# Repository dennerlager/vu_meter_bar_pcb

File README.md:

# vu_meter_bar_pcb
pi hat for vu meter bar

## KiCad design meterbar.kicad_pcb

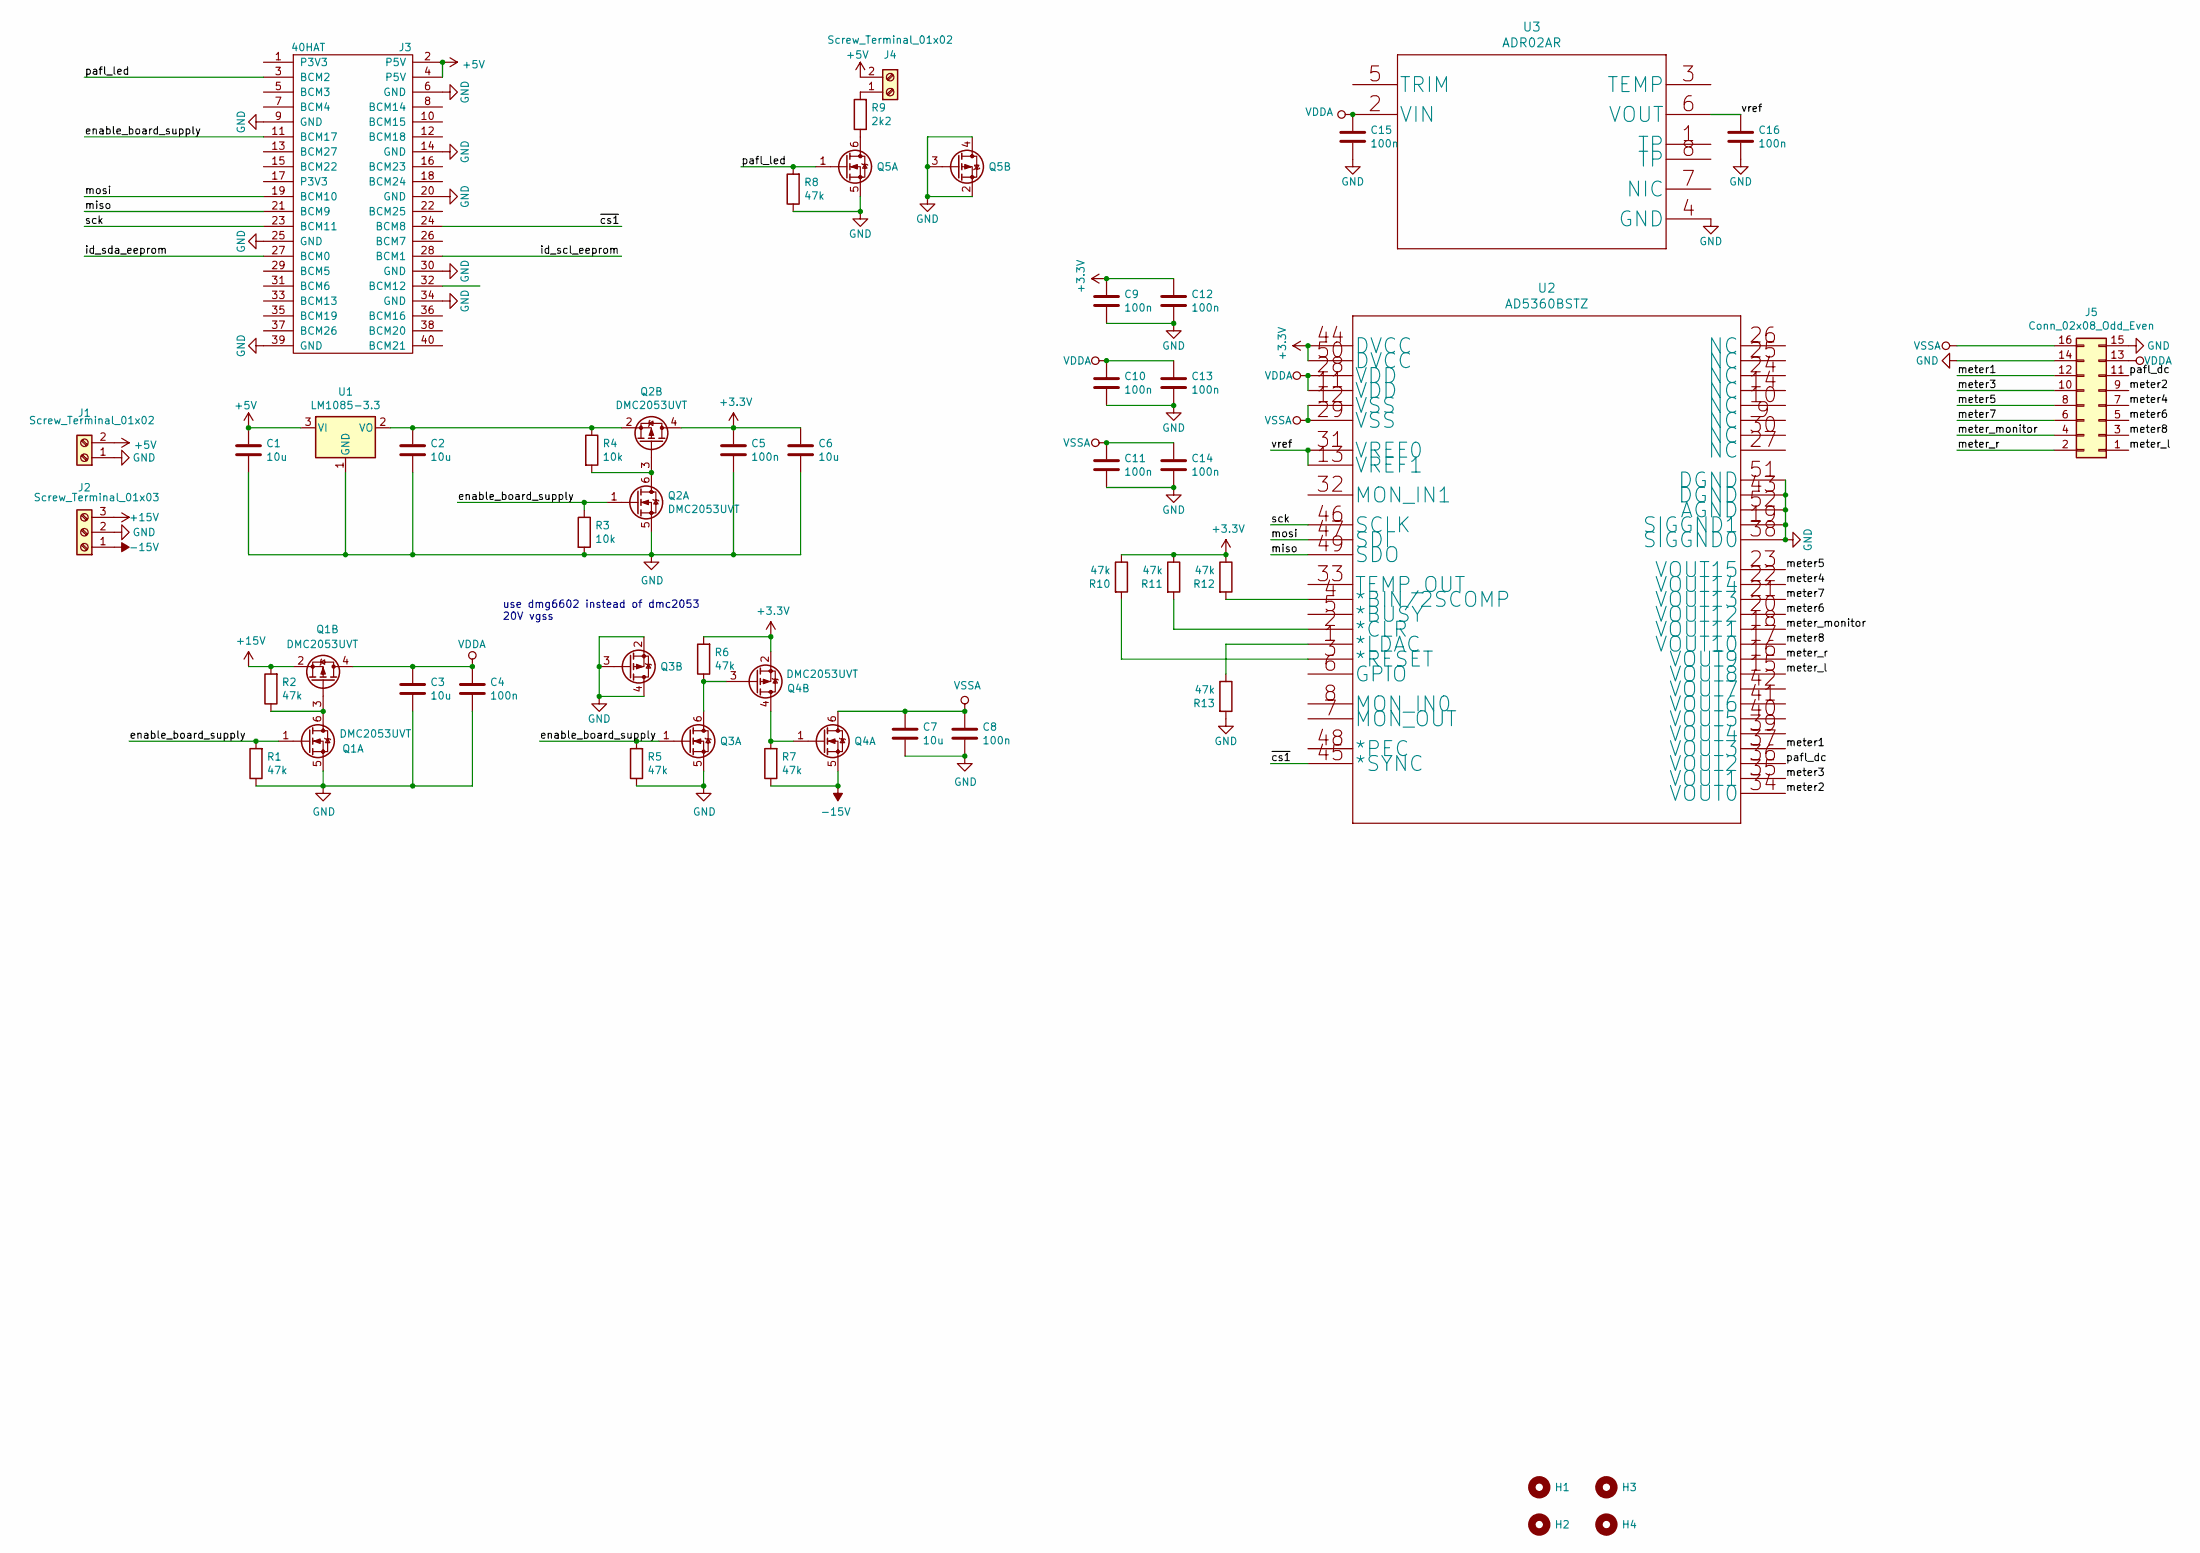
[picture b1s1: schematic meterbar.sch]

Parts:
C1, C2, C3, C6, C7: 10u; C_1206_3216Metric_Pad1.42x1.75mm_HandSolder; Voltage 20V
C4, C5, C8, C9, C10, C11, C12, C13, C14, C15, C16: 100n; C_0805_2012Metric_Pad1.15x1.40mm_HandSolder
H1, H2, H3, H4: MountingHole; MountingHole_3.2mm_M3
J1, J4: Screw_Terminal_01x02; TerminalBlock_bornier-2_P5.08mm
J2: Screw_Terminal_01x03; TerminalBlock_bornier-3_P5.08mm
J3: 40HAT; PinSocket_2x20_P2.54mm_Vertical
J5: Conn_02x08_Odd_Even; PinSocket_2x08_P2.54mm_Vertical
Q1, Q2, Q3, Q4, Q5: DMC2053UVT; TSOT-23-6
R1, R2, R5, R6, R7, R8, R10, R11, R12, R13: 47k; R_0805_2012Metric_Pad1.15x1.40mm_HandSolder
R3, R4: 10k; R_0805_2012Metric_Pad1.15x1.40mm_HandSolder
R9: 2k2; R_0805_2012Metric_Pad1.15x1.40mm_HandSolder
U1: LM1085-3.3; TO-220-3_Horizontal_TabDown
U2: AD5360BSTZ
U3: ADR02AR; ADR02ARZ

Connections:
+3V3: C5.1, C6.1, C9.1, C12.1, Q2.4 (D), Q4.2 (S), R6.2, R10.1, R11.1, R12.1, U2.44 (DVCC), U2.50 (DVCC)
+5V: C1.1, J1.2, J3.2 (P5V), J3.4 (P5V), J4.2, U1.3 (VI)
+15V: J2.3, Q1.2 (S), R2.2
-15V: J2.1, Q4.5 (S), R7.1
/enable_board_supply: J3.11 (BCM17), Q1.1 (G), Q2.1 (G), Q3.1 (G), R1.2, R3.1, R5.2
/id_scl_eeprom: J3.28 (BCM1)
/id_sda_eeprom: J3.27 (BCM0)
/meter1: J5.12, U2.37 (VOUT3)
/meter2: J5.9, U2.34 (VOUT0)
/meter3: J5.10, U2.35 (VOUT1)
/meter4: J5.7, U2.22 (VOUT14)
/meter5: J5.8, U2.23 (VOUT15)
/meter6: J5.5, U2.20 (VOUT12)
/meter7: J5.6, U2.21 (VOUT13)
/meter8: J5.3, U2.17 (VOUT10)
/meter_l: J5.1, U2.15 (VOUT8)
/meter_monitor: J5.4, U2.18 (VOUT11)
/meter_r: J5.2, U2.16 (VOUT9)
/miso: J3.21 (BCM9), U2.49 (SDO)
/mosi: J3.19 (BCM10), U2.47 (SDI)
/pafl_dc: J5.11, U2.36 (VOUT2)
/pafl_led: J3.3 (BCM2), Q5.1 (G), R8.2
/sck: J3.23 (BCM11), U2.46 (SCLK)
/vref: C16.1, U2.13 (VREF1), U2.31 (VREF0), U3.6 (VOUT)
/~cs1: J3.24 (BCM8), U2.45 (*SYNC)
GND: C1.2, C2.2, C3.2, C4.2, C5.2, C6.2, C7.2, C8.2, C9.2, C10.2, C11.2, C12.2, C13.2, C14.2, C15.2, C16.2, J1.1, J2.2, J3.6 (GND), J3.9 (GND), J3.14 (GND), J3.20 (GND), J3.25 (GND), J3.30 (GND), J3.34 (GND), J3.39 (GND), J5.14, J5.15, Q1.5 (S), Q2.5 (S), Q3.2 (S), Q3.3 (G), Q3.4 (D), Q3.5 (S), Q5.2 (S), Q5.3 (G), Q5.4 (D), Q5.5 (S), R1.1, R3.2, R5.1, R8.1, R13.2, U1.1 (GND), U2.19 (SIGGND1), U2.38 (SIGGND0), U2.43 (DGND), U2.51 (DGND), U2.52 (AGND), U3.4 (GND)
unnamed: C2.1, Q2.2 (S), R4.1, U1.2 (VO)
unnamed: J4.1, R9.2
unnamed: Q1.3 (G), Q1.6 (D), R2.1
unnamed: Q2.3 (G), Q2.6 (D), R4.2
unnamed: Q3.6 (D), Q4.3 (G), R6.1
unnamed: Q4.1 (G), Q4.4 (D), R7.2
unnamed: Q5.6 (D), R9.1
unnamed: R10.2, U2.3 (*RESET)
unnamed: R11.2, U2.2 (*CLR)
unnamed: R12.2, U2.4 (*BIN/2SCOMP)
unnamed: R13.1, U2.1 (*LDAC)
VDDA: C3.1, C4.1, C10.1, C13.1, C15.1, J5.13, Q1.4 (D), U2.11 (VDD), U2.28 (VDD), U3.2 (VIN)
VSSA: C7.1, C8.1, C11.1, C14.1, J5.16, Q4.6 (D), U2.12 (VSS), U2.29 (VSS)

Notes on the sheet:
use dmg6602 instead of dmc2053 20V vgss

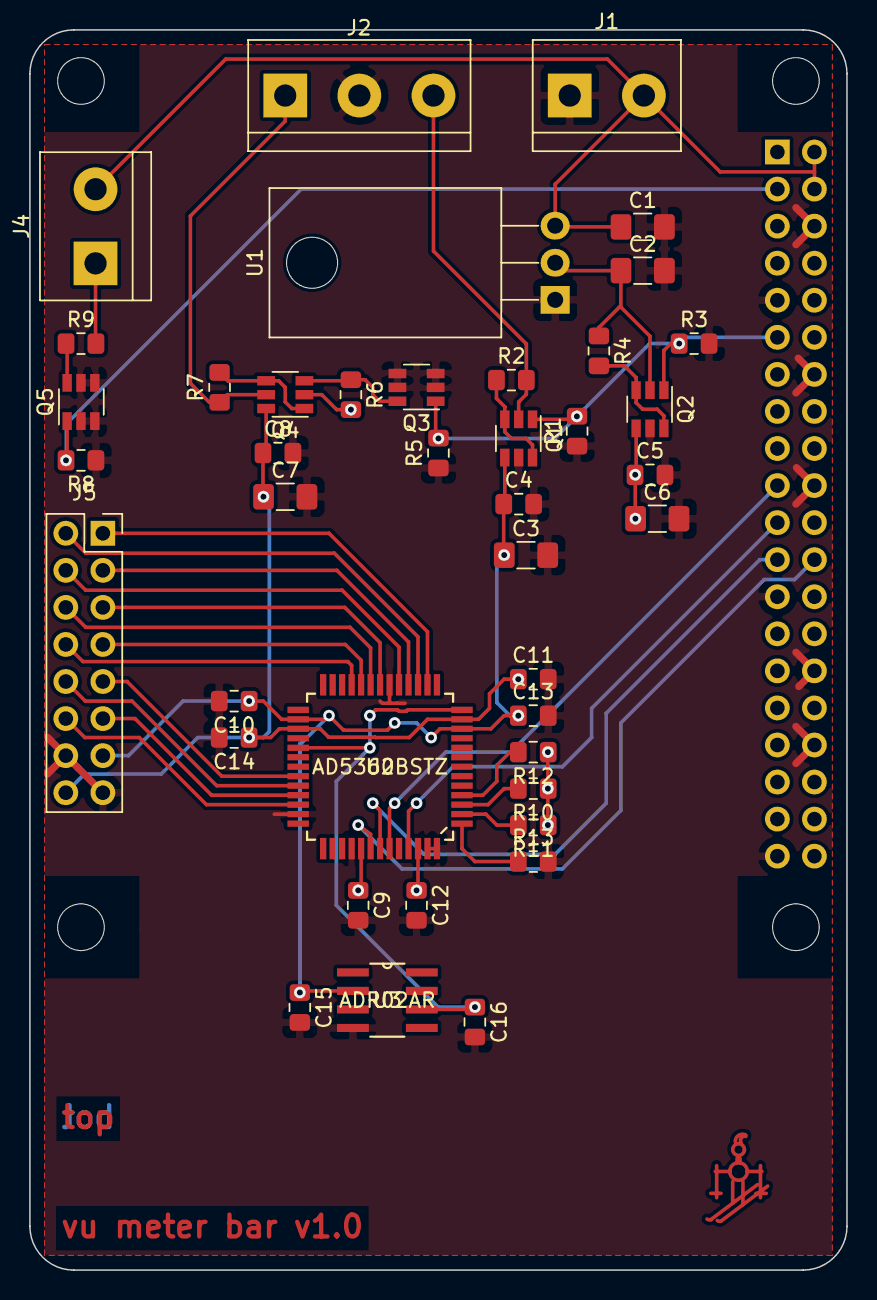
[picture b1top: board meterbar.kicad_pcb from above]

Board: 2 copper layers, 56.0 x 85.0 mm, 46 parts (1 on the bottom side), 37 nets.

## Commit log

2019-12-22 added licence
2019-12-22 first checkin
2019-12-23 ready to order
